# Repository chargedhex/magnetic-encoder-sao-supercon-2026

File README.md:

# Magnetic Encoder SAO Supercon 2026
This repo contains the information necessary for building and 3d printing the accessories for the magnetic encoder SAO I brought to Hackaday Supercon 2026

## Magnetic Encoder SAO Assembled

## Hardware Required
This project requires 6 M3 screws (I recommend 4x6mm and 2x8mm (the longer ones for the knob)) and a small (6mm diameter, 1.8mm thickness) neodymium magnet that is inserted into the knob before it's screwed together. Additionally, it requires 3 3d-printed components: a base, a knob top, and a knob shaft.
They make magnets that are magnetized radially, and many of the off-the-shelf magnetic encoder boards use those, but I had a difficult time sourcing those. I've found that it's much easier to just use the axially-magnetized neodymium magnets you can get from anywhere and design the 3d print around them like I've done here.

## Electronics Required
I have included the KiCad project in this repository, but this project requires the AS5600 8-pin ASOT or ASOM (the AS5600L uses a PWM output instead of the analog output, so it will also work, but it's not a direct replacement), 0805 resistors (2x4.7kohm and 1x330 ohm), 0805 capacitors (1x1uF and 1x100nF), an SAO connector (good options  are the SSK05-BH-254-B3 and the Wurth Elektronik 61200621621 (which I am convinced from physical comparison are the same part from the same manufacturer)), and an optional 20mmx20mm Neopixel (also known as WS2812 LEDs). The Neopixel is technically out of spec, as the datasheet says the lowest voltage it supports is 3.7V, but I have had success at the SAO standard 3.3V.

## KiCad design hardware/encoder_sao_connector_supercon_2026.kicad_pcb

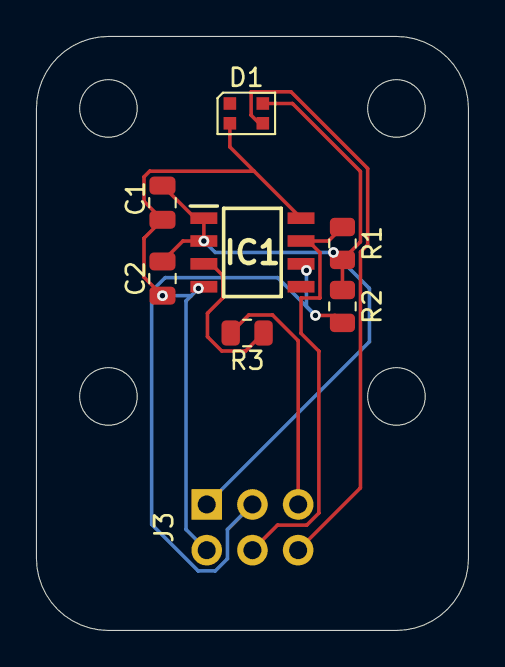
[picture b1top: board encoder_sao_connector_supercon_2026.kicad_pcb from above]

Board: 2 copper layers, 24.0 x 33.0 mm, 8 parts (1 on the bottom side), 7 nets.

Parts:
C1: 100nF; C_0805_2012Metric
C2: 1uF; C_0805_2012Metric
D1: WS2812B-2020; LED_WS2812B-2020_PLCC4_2.0x2.0mm
IC1: AS5600-ASOT
J3: Conn_02x03_Odd_Even; PinHeader_2x03_P2.54mm_Vertical
R1, R2: 4.7k; R_0805_2012Metric
R3: 330; R_0805_2012Metric

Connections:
+3V3: C1.1, C2.1, D1.4 (VDD), IC1.1 (VDD5V), IC1.2 (VDD3V3), J3.1, R1.2, R2.1
GND: C1.2, C2.2, D1.2 (VSS), IC1.4 (GND), IC1.8 (DIR), J3.2
encoder_analog_out: IC1.3 (OUT), R3.2
encoder_i2c_scl: IC1.7 (SCL), J3.4, R1.1
encoder_i2c_sda: IC1.6 (SDA), J3.3, R2.2
neopixel_data: D1.3 (DIN), J3.6
resistor_analog_out: J3.5, R3.1
